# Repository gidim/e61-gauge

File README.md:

# E61 Gauge

An analog temperature gauge for E61 espresso machines. A custom PCB drives a VID6606 stepper motor gauge needle, reading temperature from an NTC thermistor. The gauge connects via BLE to a web app for calibration and real-time monitoring.

The dial has a non-linear scale (0–150°C) with an expanded green zone at 92–97°C for precision in the critical temperature range.

<p align="center">
  
  &nbsp;
  
  &nbsp;
  
  &nbsp;
  
</p>

<p align="center">
  <a href="media/demo.mov">▶ Watch demo video</a>
</p>

---

## Hardware

Built around a **Seeed Studio XIAO nRF52840**. Key components:

- VID6606 stepper driver (SOIC-28) driving the gauge needle
- 100kΩ NTC thermistor for temperature sensing
- 2N2222A transistor switching a 5V boost converter
- Momentary button for power management (deep sleep after 10 min idle)
- JST connector for the stepper motor coils

The PCB was custom manufactured and assembled. The dial face is a custom design with a non-linear scale — the green zone (92–97°C) is expanded for precision while the cold and hot extremes are compressed. The SVG is in `hardware/dial_face.svg`. KiCad source files, schematic, and BOM are in `hardware/`.

## Enclosure

The enclosure was SLM (selective laser melting) 3D printed in metal and hand-sanded to achieve the chrome-like finish. Fusion 360 source (`enclosure/gauge_enclosure.f3z`), STEP, and STL files are in `enclosure/`.

### KiCad libraries

The schematic uses two non-standard libraries included in `libraries/`:

- `XIAO_nRF52840.pretty/` — footprint for the XIAO nRF52840 module
- `Seeed_Studio_XIAO_Series/` — schematic symbol

Add both to your KiCad library paths before opening the project.

## Firmware

Arduino sketch in `firmware/gauge/`. Uses the Adafruit nRF52 BSP.

**Dependencies** (install via Arduino Library Manager):
- `Adafruit TinyUSB`
- `Adafruit nRF52` BSP (includes `bluefruit`, `Adafruit_LittleFS`, `InternalFileSystem`)
- `AccelStepper`

The gauge supports BLE serial commands for calibration, homing, sweep tests, and configuration. See `firmware/gauge/commands.h` for the full command set.

## Web App

A Web Bluetooth app in `webapp/` — open `index.html` in Chrome (Android, macOS, or Windows). iOS Safari does not support Web Bluetooth.

Connect to the gauge over BLE to monitor temperature, set calibration points, and control the needle.

## Tools

Python utilities in `tools/` for serial-based development and testing.

```
pip install -r tools/requirements.txt
python tools/serial_terminal.py
```

## vid6606

`vid6606/` contains a standalone sweep demo sketch and a copy of the [SwitecX25](https://github.com/clearwater/SwitecX25) stepper library used for the VID6606 driver.

## test_ntc_sketch

A minimal Arduino sketch for validating NTC thermistor readings independently of the main firmware.

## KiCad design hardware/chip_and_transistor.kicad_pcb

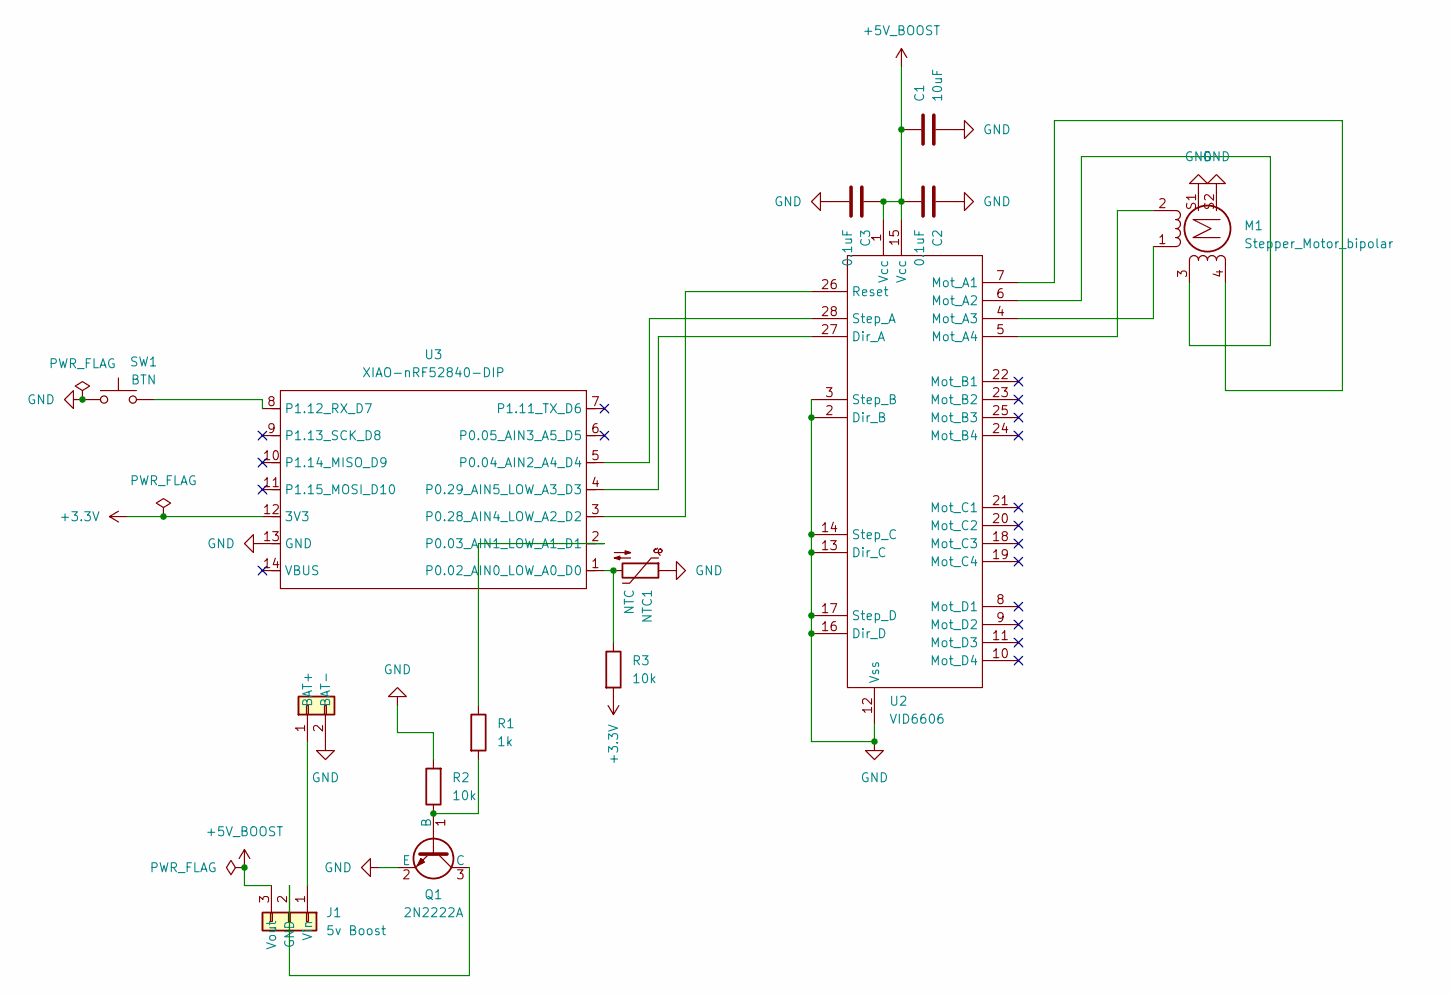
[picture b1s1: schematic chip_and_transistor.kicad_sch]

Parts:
Battery1: Battery; THT_2PAD_SOLDER_P5.08MM_GIDEON
C1: 10uF; CP_EIA-1608-08_AVX-J; LCSC C3151625
C2, C3: 0.1uF; C_0805_2012Metric; LCSC C49678
J1: 5v Boost; PinHeader_1x03_P2.54mm_Vertical; LCSC C587036
M1: Stepper_Motor_bipolar; JST_SM04B-SRSS-TB_LF__SN_; LCSC C5329994
NTC1: NTC; THT_2PAD_SOLDER_P5.08MM_GIDEON
Q1: 2N2222A; SOT-23; LCSC C82460
R1: 1k; R_0805_2012Metric; LCSC C84376
R2, R3: 10k; R_0805_2012Metric; LCSC C84376
SW1: BTN; THT_2PAD_SOLDER_P5.08MM_GIDEON
U2: VID6606; SOIC-28W_7.5x17.9mm_P1.27mm; LCSC C9900148309
U3: XIAO-nRF52840-DIP

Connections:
+3.3V: R3.2, U3.12 (3V3)
+5V_BOOST: C1.1, C2.2, C3.1, J1.3 (Vout), U2.1 (Vcc), U2.15 (Vcc)
GND: Battery1.2 (BAT-), C1.2, C2.1, C3.2, M1.S1, M1.S2, NTC1.1, Q1.2 (E), R2.2, SW1.1, U2.2 (Dir_B), U2.3 (Step_B), U2.12 (Vss), U2.13 (Dir_C), U2.14 (Step_C), U2.16 (Dir_D), U2.17 (Step_D), U3.13 (GND)
unnamed: Battery1.1 (BAT+), J1.1 (Vin)
unnamed: J1.2 (GND), Q1.3 (C)
unnamed: M1.2 (-), U2.5 (Mot_A4)
unnamed: Q1.1 (B), R1.2, R2.1
unnamed: U2.27 (Dir_A), U3.4 (P0.29_AIN5_LOW_A3_D3)
unnamed: M1.4, U2.7 (Mot_A1)
unnamed: M1.3, U2.6 (Mot_A2)
unnamed: M1.1, U2.4 (Mot_A3)
unnamed: U2.26 (Reset), U3.3 (P0.28_AIN4_LOW_A2_D2)
unnamed: U2.28 (Step_A), U3.5 (P0.04_AIN2_A4_D4)
unnamed: NTC1.2, R3.1, U3.1 (P0.02_AIN0_LOW_A0_D0)
unnamed: R1.1, U3.2 (P0.03_AIN1_LOW_A1_D1)
unnamed: SW1.2, U3.8 (P1.12_RX_D7)

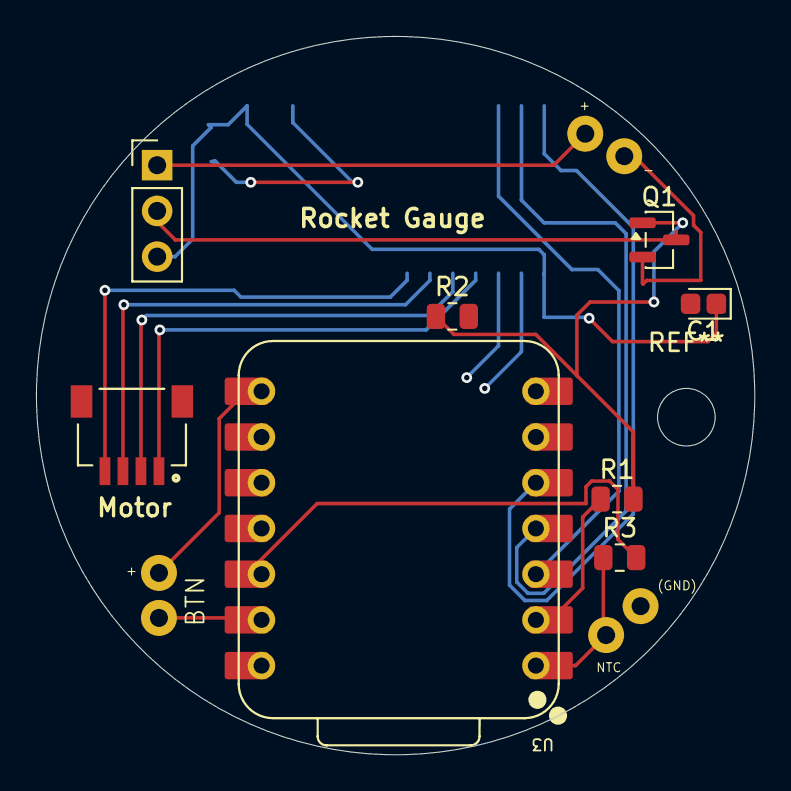
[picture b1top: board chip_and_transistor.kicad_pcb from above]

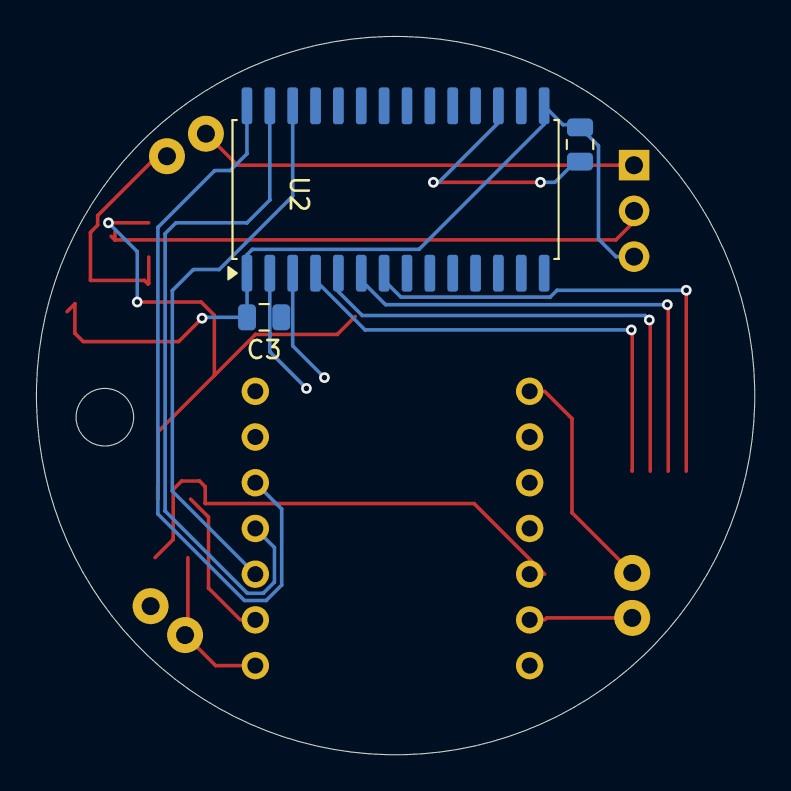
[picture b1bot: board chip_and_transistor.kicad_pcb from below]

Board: 2 copper layers, 39.9 x 39.9 mm, 14 parts (3 on the bottom side), 16 nets.

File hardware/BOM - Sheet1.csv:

Reference,Qty,Value,Assembly Status,Exclude from BOM,Footprint,Manufacturer,MPN,Datasheet
Battery1,1,Wire Connection,DNP/Hand Solder,,TestPoint:THT_2PAD_SOLDER_P5.08MM_GIDEON,N/A,N/A,~
C1,1,10 µF,Aseemble ,,Capacitor_Tantalum_SMD:CP_EIA-1608-08_AVX-J,Vishay,293D106X9010B2TE3,
"C2,C3",2,0.1uF,Assemble,,Capacitor_SMD:C_0805_2012Metric,YAGEO,CC0805KRX7R9BB104,~
J1,1,5v Boost,Assemble,,Connector_PinHeader_2.54mm:PinHeader_1x03_P2.54mm_Vertical,Molex ,22284030,~
M1,1,Stepper_Motor_bipolar,Assemble,,Connector_JST:JST_SM04B-SRSS-TB_LF__SN_,JST,SM04B-NSHSS-TB(LF)(SN),
NTC1,1,Wire Connection,DNP/Hand Solder,Exclude,TestPoint:THT_2PAD_SOLDER_P5.08MM_GIDEON,,,~
Q1,1,MMBT2222A,Assemble,,Package_TO_SOT_SMD:SOT-23,Onsemi,MMBT2222ALT1G,~
"R1,R2,R3",3,10k,Assemble,,Resistor_SMD:R_0805_2012Metric,Yageo,RC0805FR-0710KL,~
SW1,1,Wire Connection,DNP/Hand Solder,Exclude,TestPoint:THT_2PAD_SOLDER_P5.08MM_GIDEON,,,~
U2,1,VID6606,Assemble,,Package_SO:SOIC-28W_7.5x17.9mm_P1.27mm,STI,STI6606Z,
U3,1,XIAO-nRF52840-DIP,DNP/Hand Solder,Exclude,XIAO_nRF52840:XIAO-nRF52840-DIP,,,

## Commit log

2026-05-03 Initial commit: firmware, hardware, webapp, libraries
2026-05-03 Add Fusion 360 enclosure model
2026-05-03 Add media: renders, build photos, demo video
2026-05-03 Add images and video to README
2026-05-03 Fix README image layout
2026-05-03 Crop grey padding from render images
2026-05-03 Revert "Crop grey padding from render images"
    This reverts commit 1a727cae1a69c6b8b04f6bc9703c314668b65e05.
2026-05-03 Replace renders with cropped versions
2026-05-03 Use real photo as hero image
2026-05-03 Move enclosure files to top-level enclosure/
2026-05-03 Add enclosure section to README
2026-05-03 Mention custom PCB and SLM printed enclosure in README
2026-05-03 Add dial face SVG design
2026-05-03 Mention custom dial face in README
2026-05-03 Fix description: gauge is for E61 machines, not rocket-specific
2026-05-03 Rename to E61 Gauge in README
2026-05-03 Add CC BY-SA 4.0 license
2026-05-03 Add PCB 3D render to media and README
2026-05-03 Replace PCB render with cropped version
2026-05-03 Rename PCB render to bust GitHub image cache
2026-05-03 Update README to use renamed PCB render
2026-05-04 Disable VBAT_ENABLE before deep sleep to prevent battery divider drain
2026-05-04 Fix sleep: disable SoftDevice before System OFF, de-energize motor coils
2026-05-04 Add TODO list
